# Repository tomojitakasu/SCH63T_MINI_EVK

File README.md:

# **SCHA63T_MINI_EVK**

## **Overview**

SCHA63T_MINI_EVK is a compact USB 2.0 interface board for Murata 6 DOF MEMS-IMU
SCHA63T-K03. The IMU sensor sampling timing can be synchronized by PPS and
NMEA inputs from an external clock source.

--------------------------------------------------------------------------------

## **Package Structure**
```
SCHA63T_MINI_EVK --+-- FW      Firmware source programs for Seeeduino XIAO
                   |           (ref [3])
                   +-- HW      I/F Board CAD data and parts list for hardware
                   |           (*.brd and *.sch are for Eagle)
                   +-- doc     SCHA63T-K03 documents (ref [1][2])
```

--------------------------------------------------------------------------------

## **Installation**

* Download and install Arduino IDE to your PC by "Software Step 1" in ref [3].

* Extract PocketSDR.zip to an appropriate directory <install_dir>.

* In Arduino IDE, execute menu File - Open... and select the sketch file
<install_dir>\SCHA63T_MIN_EVK\FW\Arduino\SCHA63T\SCHA63T.ino.

* Execute menu Sketch - Verify/Compile to compile the sketch.

* Connect SCHA63T_MINI_EVK board to the PC. Reset Seeeduino XIAO by shorting
the RST pins twice to enter the boot mode.

* Execute menu Tools - Board "Seeeduino XIAO" - Seeed SAMD (32-bits ARM
Cortex-M0+ and Cortex-M4) Boards - Seeeduino XIAO.

* Execute menu Tools - Port - COMxx (Seeeduino XIAO).

* Execute menu Sketch - Upload. If you see "Verify successful" in the IDE
message window, the firmware is properly written to the board.

--------------------------------------------------------------------------------

## **Operation**

* After connecting the SCHA63T_MINI_EVK board to the PC by USB cable, the board
automatically starts to output the IMU data as the following format via the USB
serial port. The initial output data rate is 100 Hz.
```
  $IMU,<t_sync>,<time>,<Rx>,<Ry>,<Rz>,<Ax>,<Ay>,<Az>,<temp>,<stat>*<CS>\r\n

  <t_sync>   : External time sync status (0:async, 1: PPS, 2: PPS + NMEA)
  <time>     : Time tag (s) (time of day in UTC for <t_sync> = 2)
  <Rx>,<Ry>,<Rz> : Gyroscope X,Y,Z data (deg/H)
  <Ax>,<Ay>,<Az> : Accelerometer X,Y,Z data (g)
  <temp>     : Sensor temperature (C)
  <stat>     : Sensor summary status (HEX) (0: OK, 1: error)
               bit 6-4: Rx,Ry,Rz, bit 2-0: Ax,Ay,Az
  <CS>       : Checksum same as NMEA
```

* By inputting PPS and NMEA signals via the external sync connector of the
board, the sampling timing of the IMU can be synchronized to the external
clock source. The pin assignment of the external sync connector is as follows.
Without the sync signals, the sampling is done by the internal clock.
```
  JST SH 3P (TOP VIEW)
  +-------+
  | pin 3 | <---- NMEA (3.3V, 9600 bps, GxGGA or GxRMC)
  | pin 2 | <---- PPS  (3.3V, rising edge)
  | pin 1 | ----- GND
  +-------+
```

* By sending commands to the board via the USB serial port, some IMU or
sampling parameters can be configured. The commands are as follows. The max
data rate is 200 Hz.
```
  reset                        : Reset device.
  device                       : Show device information.
  start                        : Start output data.
  stop                         : Stop output data.
  status                       : Show status.
  rate [<rate>]                : Set output data rate (Hz).
  range [<range_g> <range_a>]  : Select dynamic range gyro/accel.
                                 (0:300deg/H or 6g, 1:150deg/H or 1.5g)
  filter [<filt_g> <filt_a>]   : Select filter gyro/accel.
                                 (0:13Hz, 1:20Hz, 2:46Hz, 3:200Hz, 4:300Hz)
  table                        : Show cross-axis compensation table.
  read {DUE|UNO} [<addr>]      : Read device register(s). (addr:HEX)
  write {DUE|UNO} <addr> <val> : Write device register. (addr/val:HEX)
  debug [<level>]              : Set debug level. (0:no debug)
  help                         : Show command help.
```

--------------------------------------------------------------------------------

## **References**

[1] Murata, SCHA63T-K03 Data Sheet, Rev 1, 2021

[2] Murata, Assembly instructions for SCHA600 series Technical Note Rev 1.0, 2021

[3] Seeed Wiki, Getting Started with Seeeduino XIAO
(https://wiki.seeedstudio.com/Seeeduino-XIAO)

--------------------------------------------------------------------------------

## **History**

- 2022-03-11  1.0  1st version

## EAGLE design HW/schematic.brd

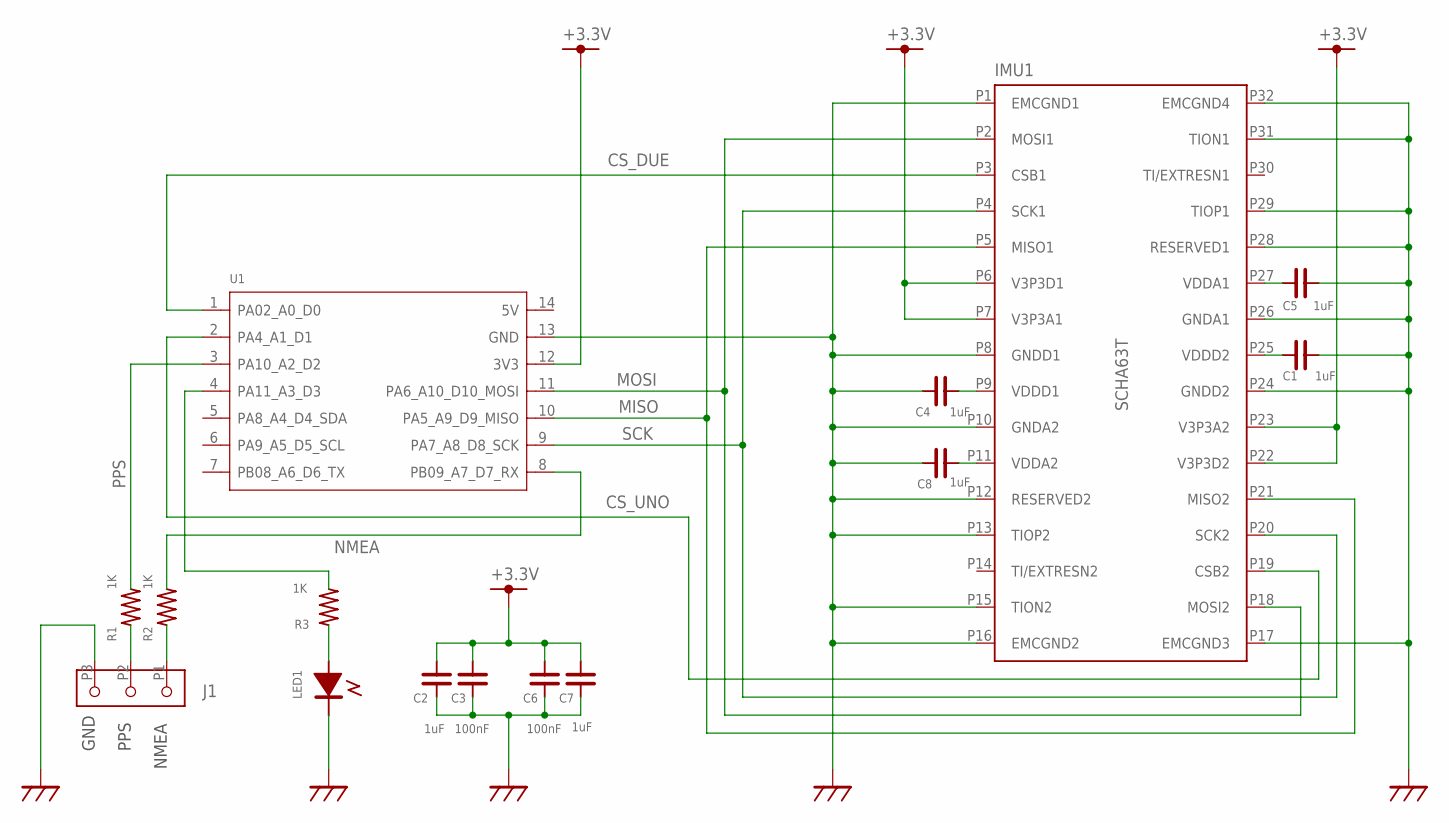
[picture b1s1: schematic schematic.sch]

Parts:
C1, C2, C4, C5, C7, C8: 1uF; C1608
C3, C6: 100nF; C1608
IMU1: SCHA63T; SOIC-32
J1: JST_SH_10_3P
LED1: LED1608; LED_1608
R1, R2, R3: 1K; C1608
U1: MOUDLE-SEEEDUINO-XIAO; MOUDLE14P-2.54-21X17.8MM

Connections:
+3.3V: C2.2, C3.2, C6.2, C7.2, IMU1.P6 (V3P3D1), IMU1.P7 (V3P3A1), IMU1.P22 (V3P3D2), IMU1.P23 (V3P3A2), U1.12 (3V3)
CS_DUE: IMU1.P3 (CSB1), U1.1 (PA02_A0_D0)
CS_UNO: IMU1.P19 (CSB2), U1.2 (PA4_A1_D1)
GND: C1.2, C2.1, C3.1, C4.1, C5.2, C6.1, C7.1, C8.1, IMU1.P1 (EMCGND1), IMU1.P8 (GNDD1), IMU1.P10 (GNDA2), IMU1.P12 (RESERVED2), IMU1.P13 (TIOP2), IMU1.P15 (TION2), IMU1.P16 (EMCGND2), IMU1.P17 (EMCGND3), IMU1.P24 (GNDD2), IMU1.P26 (GNDA1), IMU1.P28 (RESERVED1), IMU1.P29 (TIOP1), IMU1.P31 (TION1), IMU1.P32 (EMCGND4), J1.P3, LED1.2, U1.13 (GND)
MISO: IMU1.P5 (MISO1), IMU1.P21 (MISO2), U1.10 (PA5_A9_D9_MISO)
MOSI: IMU1.P2 (MOSI1), IMU1.P18 (MOSI2), U1.11 (PA6_A10_D10_MOSI)
unnamed: C5.1, IMU1.P27 (VDDA1)
unnamed: C1.1, IMU1.P25 (VDDD2)
unnamed: C4.2, IMU1.P9 (VDDD1)
unnamed: C8.2, IMU1.P11 (VDDA2)
unnamed: J1.P2, R1.1
unnamed: J1.P1, R2.1
unnamed: LED1.1 (+), R3.1
unnamed: R3.2, U1.4 (PA11_A3_D3)
NMEA: R2.2, U1.8 (PB09_A7_D7_RX)
PPS: R1.2, U1.3 (PA10_A2_D2)
SCK: IMU1.P4 (SCK1), IMU1.P20 (SCK2), U1.9 (PA7_A8_D8_SCK)

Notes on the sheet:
PPS
NMEA
GND

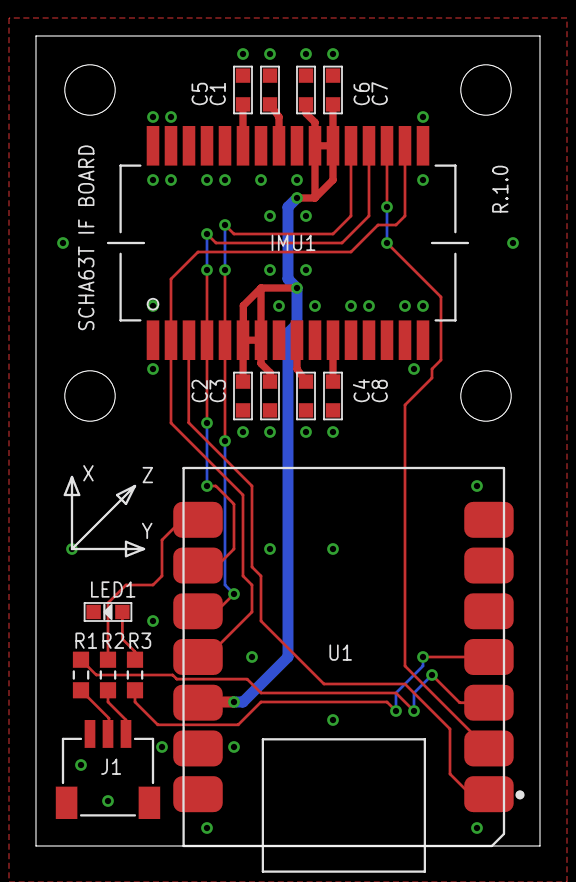
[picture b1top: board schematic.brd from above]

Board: 2 copper layers, 28.0 x 45.0 mm, 15 parts (0 on the bottom side), 17 nets.

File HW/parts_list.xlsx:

No | Part | Value | Package | Supplier | Supplier Part Number | Digi-Key Part Number | URL
1 | IMU1 | SCHA63T-K03 | SOIC-32 | Murata | SCHA63T-K03-05 | 490-SCHA63T-K03-05CT-ND | https://www.digikey.jp/product-detail/ja/murata-electronics/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
2 | U1 | MOUDLE-SEEEDUINO-XIAO | 21 x 17.8 mm, 14P-2.54 mm | Seeed | Seeediuino XIAO | - | https://wiki.seeedstudio.com/Seeeduino-XIAO/
3 | C1 | 1uF | C1608
4 | C2 | 1uF | C1608
5 | C3 | 100nF | C1608
6 | C4 | 1uF | C1608
7 | C5 | 1uF | C1608
8 | C6 | 100nF | C1608
9 | C7 | 1uF | C1608
10 | C8 | 1uF | C1608
11 | R1 | 1K | R1608
12 | R2 | 1K | R1608
13 | R3 | 1K | R1608
14 | LED1 | LED1608 | LED1608
15 | J1 | Conn Header SMD R/A 3P 1mm | 4.25 x 5.0 x 2.9 mm | JST | SM03B-SRSS-TB(LF)(SN) | 455-1803-1-ND | https://www.digikey.jp/product-detail/ja/jst-sales-america-i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

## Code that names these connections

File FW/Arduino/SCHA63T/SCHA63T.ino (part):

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#define DEV_NAME     "SCHA63T-K03" // device name
#define FW_VER       "1.0.0"  // F/W version

#define CS_DUE       0        // Seeeduino XIAO PIN 1: (O) SPI CS DUE
#define CS_UNO       1        // Seeeduino XIAO PIN 2: (O) SPI CS UNO
#define PPS          2        // Seeeduino XIAO PIN 3: (I) PPS
#define LED_PPS      3        // Seeeduino XIAO PIN 4: (O) PPS LED
#define TEST_PIN     4        // Seeeduino XIAO PIN 5: (O) TEST PIN
#define LED_T        11       // Seeeduino XIAO LED T: (O) (blue)
#define LED_R        12       // Seeeduino XIAO LED R: (O) (blue)
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#define SCALE_TEMP (1.0/30)   // SCHA63T temperature scale (C/LSB)

#define HOST_RATE    115200   // HOST bitrate (bps)
#define NMEA_RATE    9600     // NMEA bitrate (bps)
#define PPS_MODE     RISING   // PPS interface mode (RISING or FALLING)
#define SAMP_RATE    200      // sampling rate (Hz)
#define MAX_RATE     200      // max data output rate (Hz)
#define MAX_TRY_INIT 3        // max try of device initializtion
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char buff_command[128];       // command buffer
int p_command = 0;            // command buffer pointer
char buff_nmea[128];          // NMEA sentense buffer
int p_nmea = 0;               // NMEA sentense buffer pointer

// cross-axis compensation table ([1] 2.6)
float Cx[3][3] = {{1, 0, 0}, {0, 1, 0}, {0, 0, 1}}; // gyro
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
// STARTUP routine -------------------------------------------------------------
void setup() {  
  pinMode(CS_DUE, OUTPUT);
  pinMode(CS_UNO, OUTPUT);
  pinMode(PPS, INPUT_PULLUP);
  pinMode(TEST_PIN, OUTPUT);
  pinMode(LED_PPS, OUTPUT);
  
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  delay(100);
  
  // start PPS interrupts
  attachInterrupt(digitalPinToInterrupt(PPS), pps_ISR, PPS_MODE);
  delay(100);
  
  // start NMEA serials
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  
  if (time_sync == 0) {
    trace(3, "PPS signal detected: time=%.3f\r\n", time_ms * 0.001);
    time_sync = 1; // external time sync mode = PPS
  }
  time_ms = time_ms / 1000 * 1000;
  samp_count = 0;
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
// command - status ------------------------------------------------------------
void command_status(const char *buff) {
    static const char *str_tsync[] = {"async", "PPS", "PPS+NMEA"};
    double time = time_ms * 0.001, hms[3];
    
    hms[0] = floor(time / 3600.0);
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    if (i == 0) sscanf(p, ",%2d%2d%2d", time, time + 1, time + 2);
  }
  noInterrupts();
  time_sync = 2; // external time sync mode = PPS+NMEA
  time_ms = (((time[0] * 60) + time[1]) * 60 + time[2]) * 1000 + time_ms % 1000;
  interrupts();
  
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
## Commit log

2022-03-11 new repository
2022-03-11 Update License.
2022-03-11 Added.
